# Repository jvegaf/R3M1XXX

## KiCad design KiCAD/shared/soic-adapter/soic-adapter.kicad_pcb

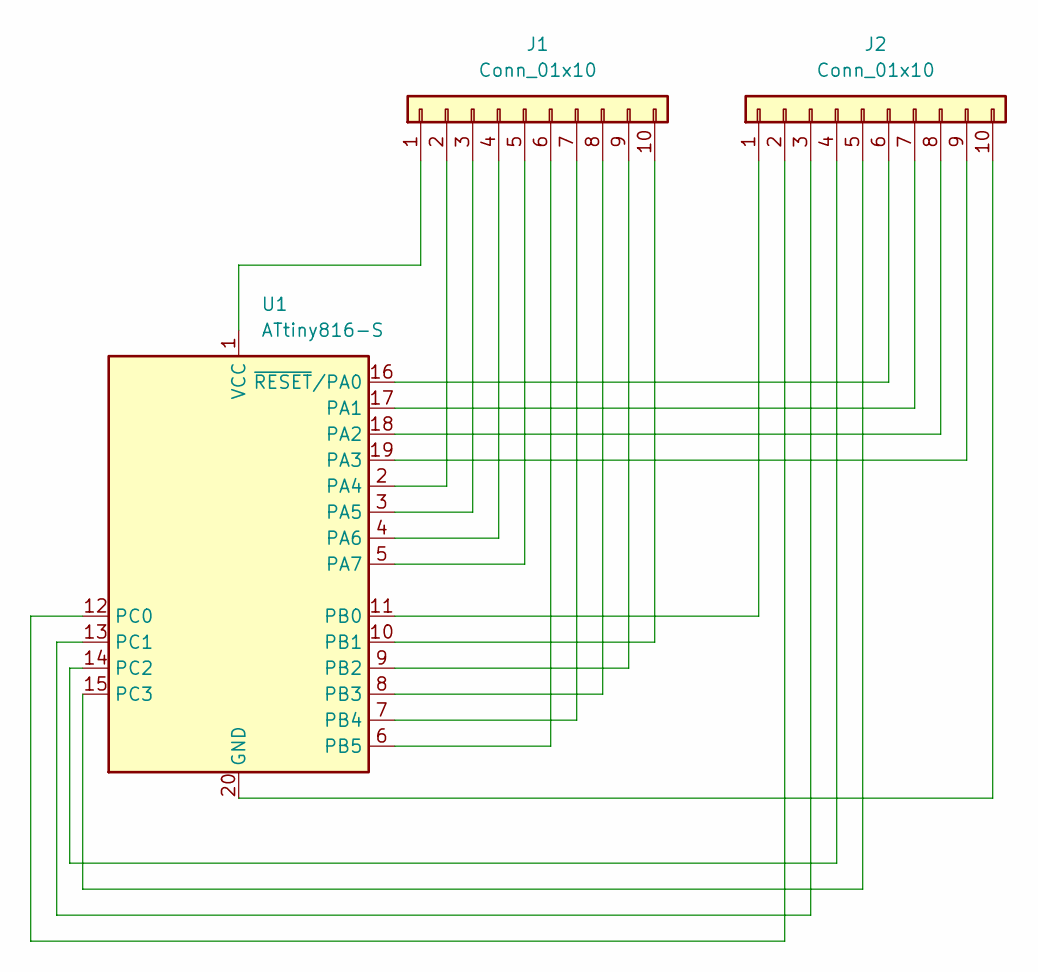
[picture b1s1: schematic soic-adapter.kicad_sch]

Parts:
J1: Conn_01x10; PinHeader_1x10_P2.54mm_Vertical
J2: Conn_01x10; PinSocket_1x10_P2.54mm_Vertical
U1: ATtiny816-S; SOIC-20W_7.5x12.8mm_P1.27mm

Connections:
unnamed: J1.1, U1.1 (VCC)
unnamed: J1.2, U1.2 (PA4)
unnamed: J1.3, U1.3 (PA5)
unnamed: J1.4, U1.4 (PA6)
unnamed: J1.5, U1.5 (PA7)
unnamed: J1.6, U1.6 (PB5)
unnamed: J1.7, U1.7 (PB4)
unnamed: J1.8, U1.8 (PB3)
unnamed: J1.9, U1.9 (PB2)
unnamed: J1.10, U1.10 (PB1)
unnamed: J2.1, U1.11 (PB0)
unnamed: J2.2, U1.12 (PC0)
unnamed: J2.3, U1.13 (PC1)
unnamed: J2.4, U1.14 (PC2)
unnamed: J2.5, U1.15 (PC3)
unnamed: J2.6, U1.16 (~RESET/PA0)
unnamed: J2.7, U1.17 (PA1)
unnamed: J2.8, U1.18 (PA2)
unnamed: J2.9, U1.19 (PA3)
unnamed: J2.10, U1.20 (GND)

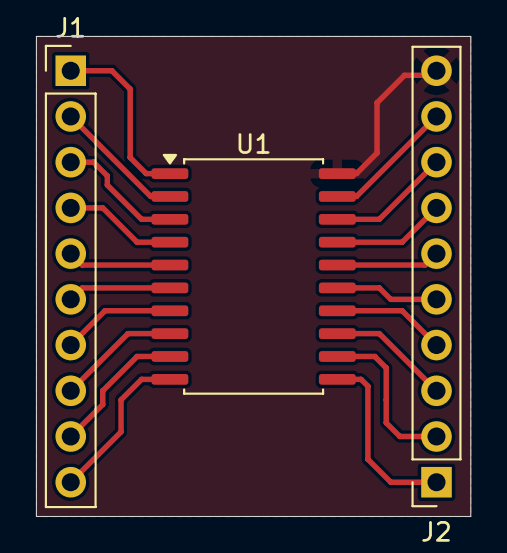
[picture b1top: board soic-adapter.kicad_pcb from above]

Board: 2 copper layers, 24.1 x 26.7 mm, 3 parts (0 on the bottom side), 20 nets.

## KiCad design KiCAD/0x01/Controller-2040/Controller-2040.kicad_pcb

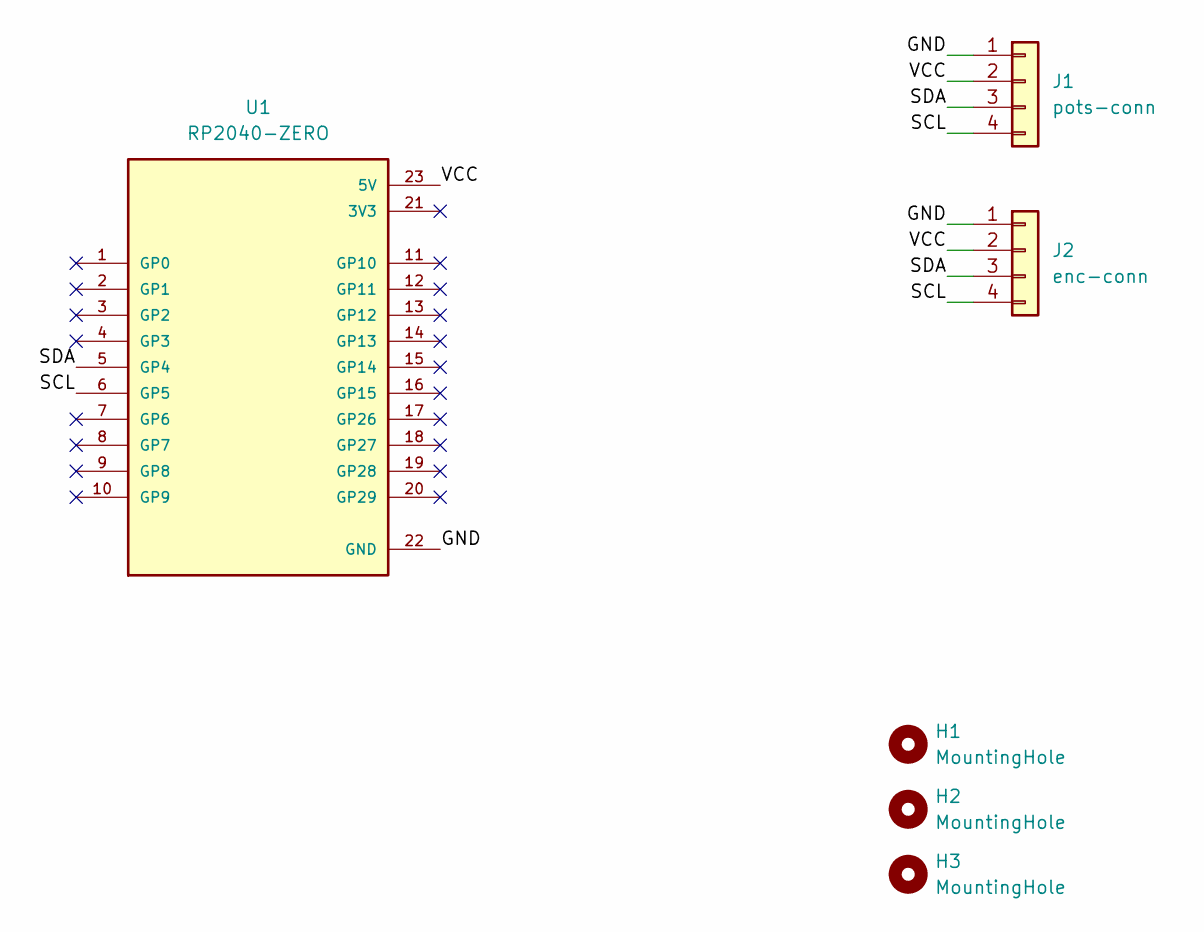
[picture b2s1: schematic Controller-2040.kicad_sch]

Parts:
H1, H2, H3: MountingHole; MountingHole_3.2mm_M3
J1: pots-conn; JST_PH_S4B-PH-K_1x04_P2.00mm_Horizontal
J2: enc-conn; JST_PH_S4B-PH-K_1x04_P2.00mm_Horizontal
U1: RP2040-ZERO; MODULE_RP2040-ZEROa; PARTREV NA

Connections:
/GND: J1.1, J2.1, U1.22 (GND)
/SCL: J1.4, J2.4, U1.6 (GP5)
/SDA: J1.3, J2.3, U1.5 (GP4)
/VCC: J1.2, J2.2, U1.23 (5V)

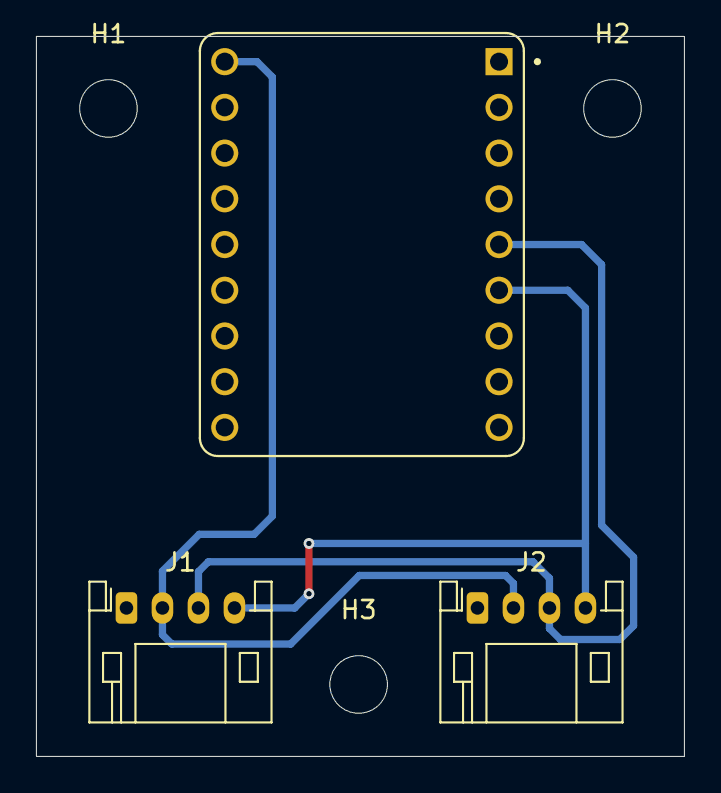
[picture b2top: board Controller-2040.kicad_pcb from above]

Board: 2 copper layers, 36.0 x 40.0 mm, 6 parts (0 on the bottom side), 4 nets.

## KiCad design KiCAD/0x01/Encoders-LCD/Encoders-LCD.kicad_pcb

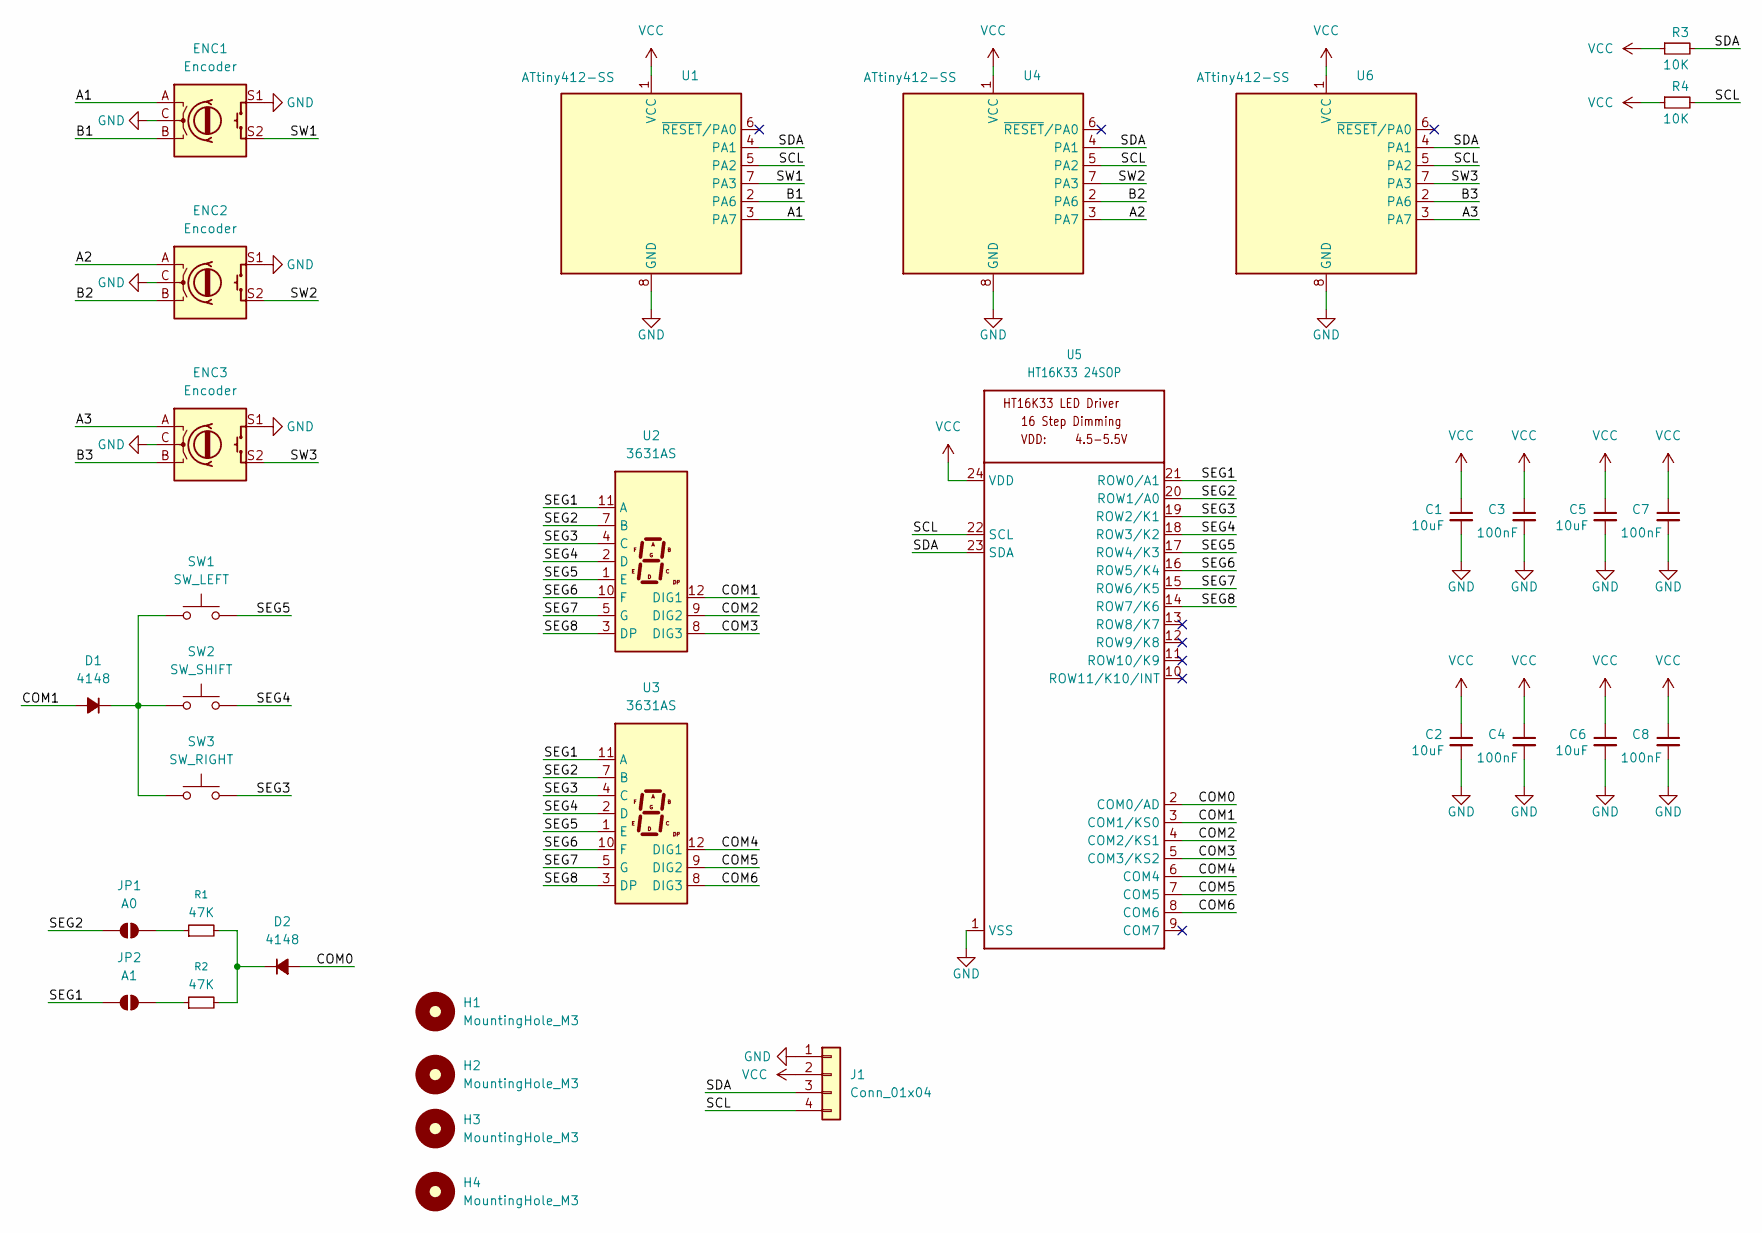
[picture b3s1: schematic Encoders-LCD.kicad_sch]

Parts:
C1, C2, C5, C6: 10uF; C_0805_2012Metric_Pad1.18x1.45mm_HandSolder
C3, C4, C7, C8: 100nF; C_0603_1608Metric_Pad1.08x0.95mm_HandSolder
D1, D2: 4148; D_SOD-123
ENC1, ENC2, ENC3: Encoder; self-RotaryEncoder_Alps_EC11E-Switch_Vertical_H20mm_Circula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
H1, H2, H3, H4: MountingHole_M3; MountingHole_3.2mm_M3
J1: Conn_01x04; JST_PH_S4B-PH-K_1x04_P2.00mm_Horizontal
JP1: A0; SolderJumper-2_P1.3mm_Open_RoundedPad1.0x1.5mm
JP2: A1; SolderJumper-2_P1.3mm_Open_RoundedPad1.0x1.5mm
R1, R2: 47K; R_0805_2012Metric_Pad1.20x1.40mm_HandSolder
R3, R4: 10K; C_0805_2012Metric_Pad1.18x1.45mm_HandSolder
SW1: SW_LEFT; SW_PUSH_6mm_H4.3mm
SW2: SW_SHIFT; SW_PUSH_6mm_H4.3mm
SW3: SW_RIGHT; SW_PUSH_6mm_H4.3mm
U1, U4, U6: ATtiny412-SS; SOIC-8_3.9x4.9mm_P1.27mm
U2, U3: 3631AS
U5: HT16K33 24SOP; SOP-24_7.5x15.4mm_P1.27mm

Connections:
/A1: ENC1.A, U1.3 (PA7)
/A2: ENC2.A, U4.3 (PA7)
/A3: ENC3.A, U6.3 (PA7)
/B1: ENC1.B, U1.2 (PA6)
/B2: ENC2.B, U4.2 (PA6)
/B3: ENC3.B, U6.2 (PA6)
/COM0: D2.2 (A), U5.2 (COM0/AD)
/COM1: D1.2 (A), U2.12 (DIG1), U5.3 (COM1/KS0)
/COM2: U2.9 (DIG2), U5.4 (COM2/KS1)
/COM3: U2.8 (DIG3), U5.5 (COM3/KS2)
/COM4: U3.12 (DIG1), U5.6 (COM4)
/COM5: U3.9 (DIG2), U5.7 (COM5)
/COM6: U3.8 (DIG3), U5.8 (COM6)
/SCL: J1.4, R4.2, U1.5 (PA2), U4.5 (PA2), U5.22 (SCL), U6.5 (PA2)
/SDA: J1.3, R3.2, U1.4 (PA1), U4.4 (PA1), U5.23 (SDA), U6.4 (PA1)
/SEG1: JP2.1 (A), U2.11 (A), U3.11 (A), U5.21 (ROW0/A1)
/SEG2: JP1.1 (A), U2.7 (B), U3.7 (B), U5.20 (ROW1/A0)
/SEG3: SW3.2, U2.4 (C), U3.4 (C), U5.19 (ROW2/K1)
/SEG4: SW2.2, U2.2 (D), U3.2 (D), U5.18 (ROW3/K2)
/SEG5: SW1.2, U2.1 (E), U3.1 (E), U5.17 (ROW4/K3)
/SEG6: U2.10 (F), U3.10 (F), U5.16 (ROW5/K4)
/SEG7: U2.5 (G), U3.5 (G), U5.15 (ROW6/K5)
/SEG8: U2.3 (DP), U3.3 (DP), U5.14 (ROW7/K6)
/SW1: ENC1.S2, U1.7 (PA3)
/SW2: ENC2.S2, U4.7 (PA3)
/SW3: ENC3.S2, U6.7 (PA3)
GND: C1.2, C2.2, C3.2, C4.2, C5.2, C6.2, C7.2, C8.2, ENC1.C, ENC1.S1, ENC2.C, ENC2.S1, ENC3.C, ENC3.S1, J1.1, U1.8 (GND), U4.8 (GND), U5.1 (VSS), U6.8 (GND)
unnamed: D1.1 (K), SW1.1, SW2.1, SW3.1
unnamed: D2.1 (K), R1.2, R2.2
unnamed: JP1.2 (B), R1.1
unnamed: JP2.2 (B), R2.1
VCC: C1.1, C2.1, C3.1, C4.1, C5.1, C6.1, C7.1, C8.1, J1.2, R3.1, R4.1, U1.1 (VCC), U4.1 (VCC), U5.24 (VDD), U6.1 (VCC)

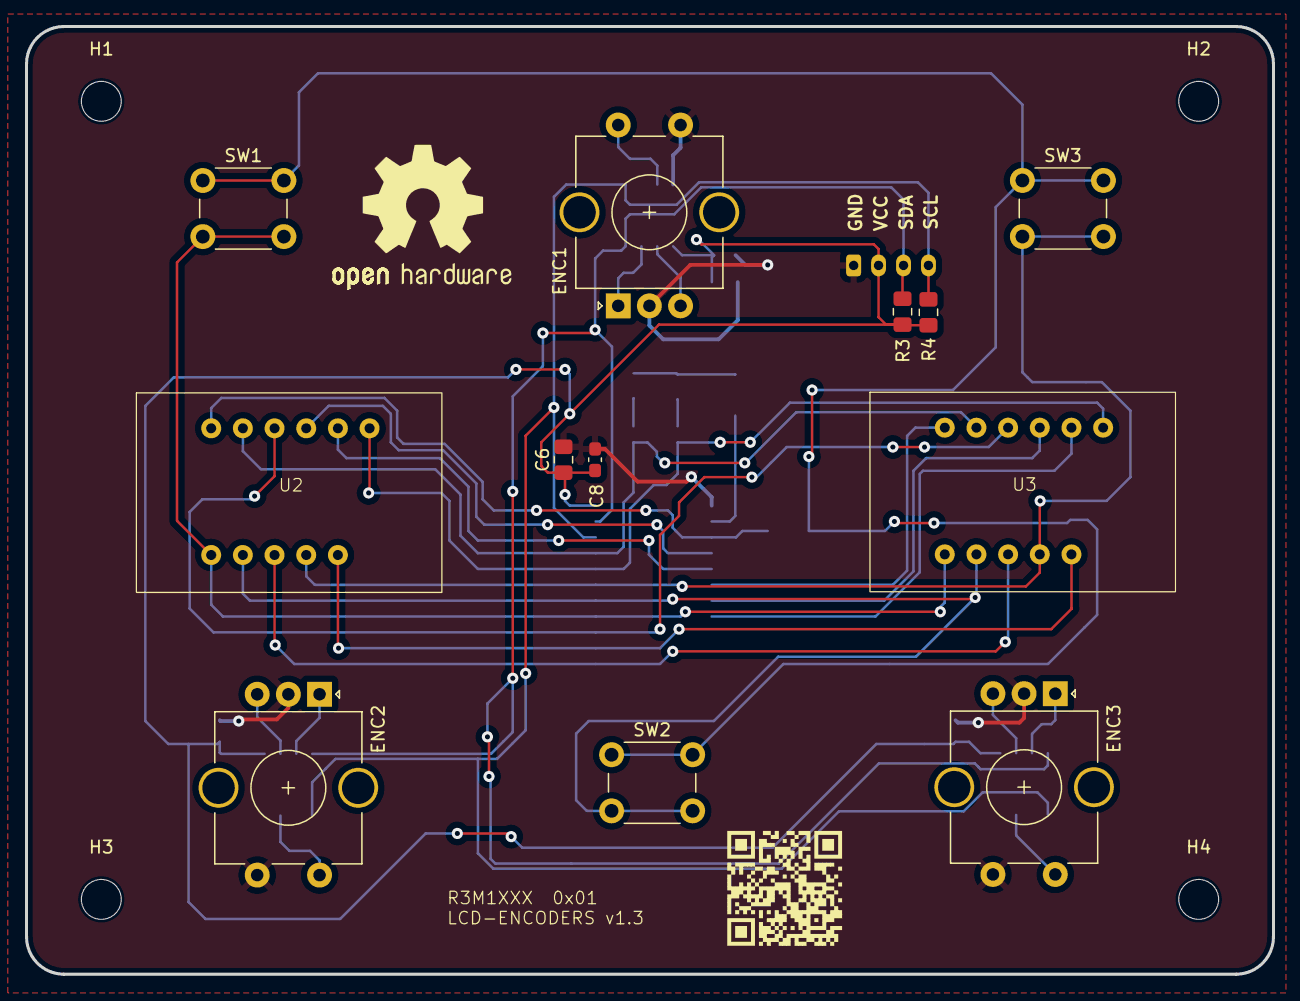
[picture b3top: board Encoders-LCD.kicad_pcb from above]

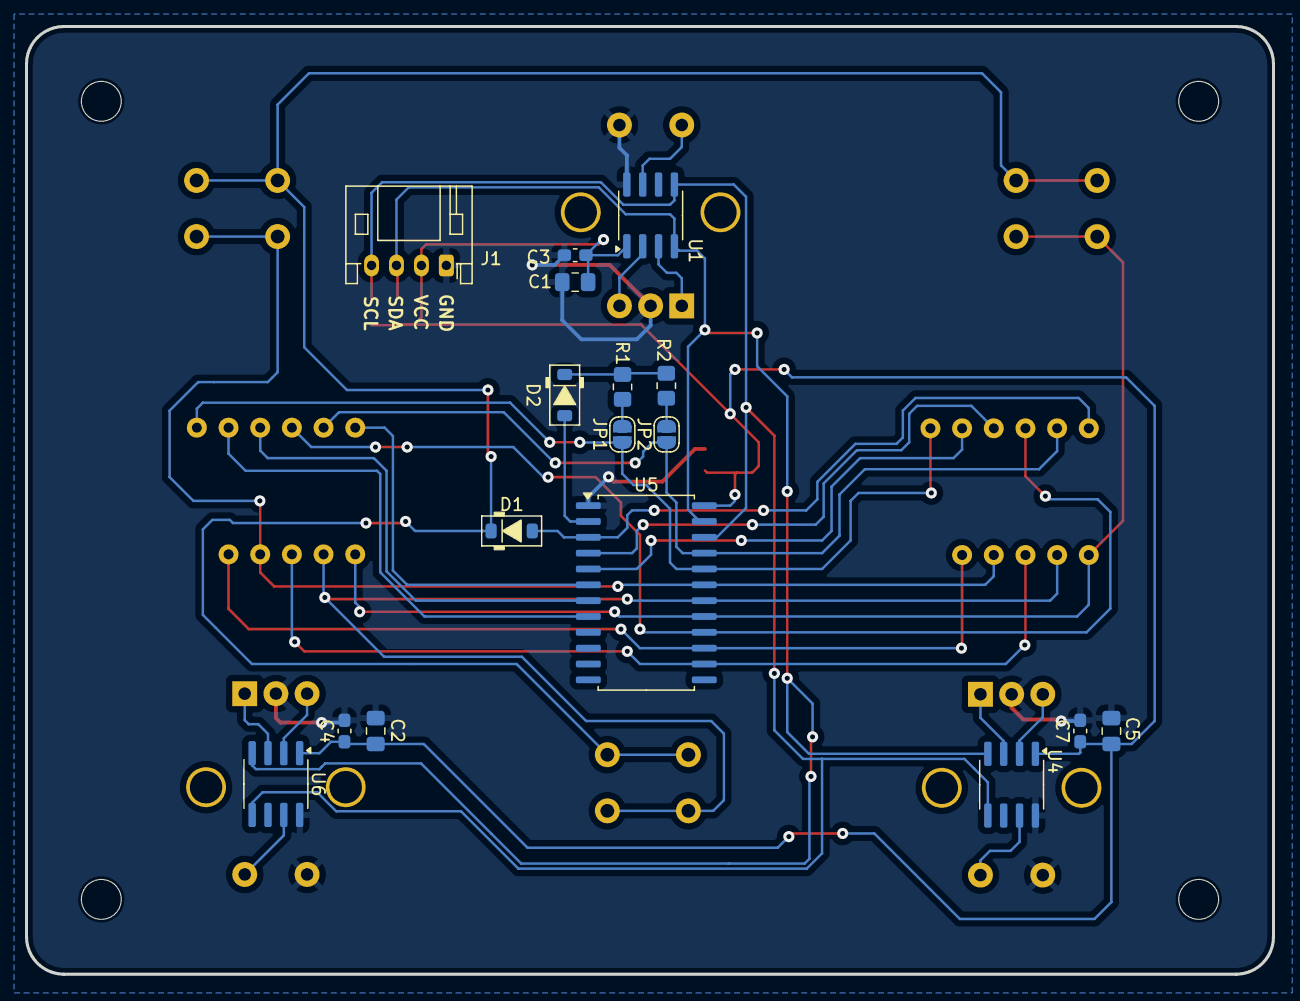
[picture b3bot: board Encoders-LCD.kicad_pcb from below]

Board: 2 copper layers, 100.0 x 76.0 mm, 33 parts (17 on the bottom side), 32 nets.

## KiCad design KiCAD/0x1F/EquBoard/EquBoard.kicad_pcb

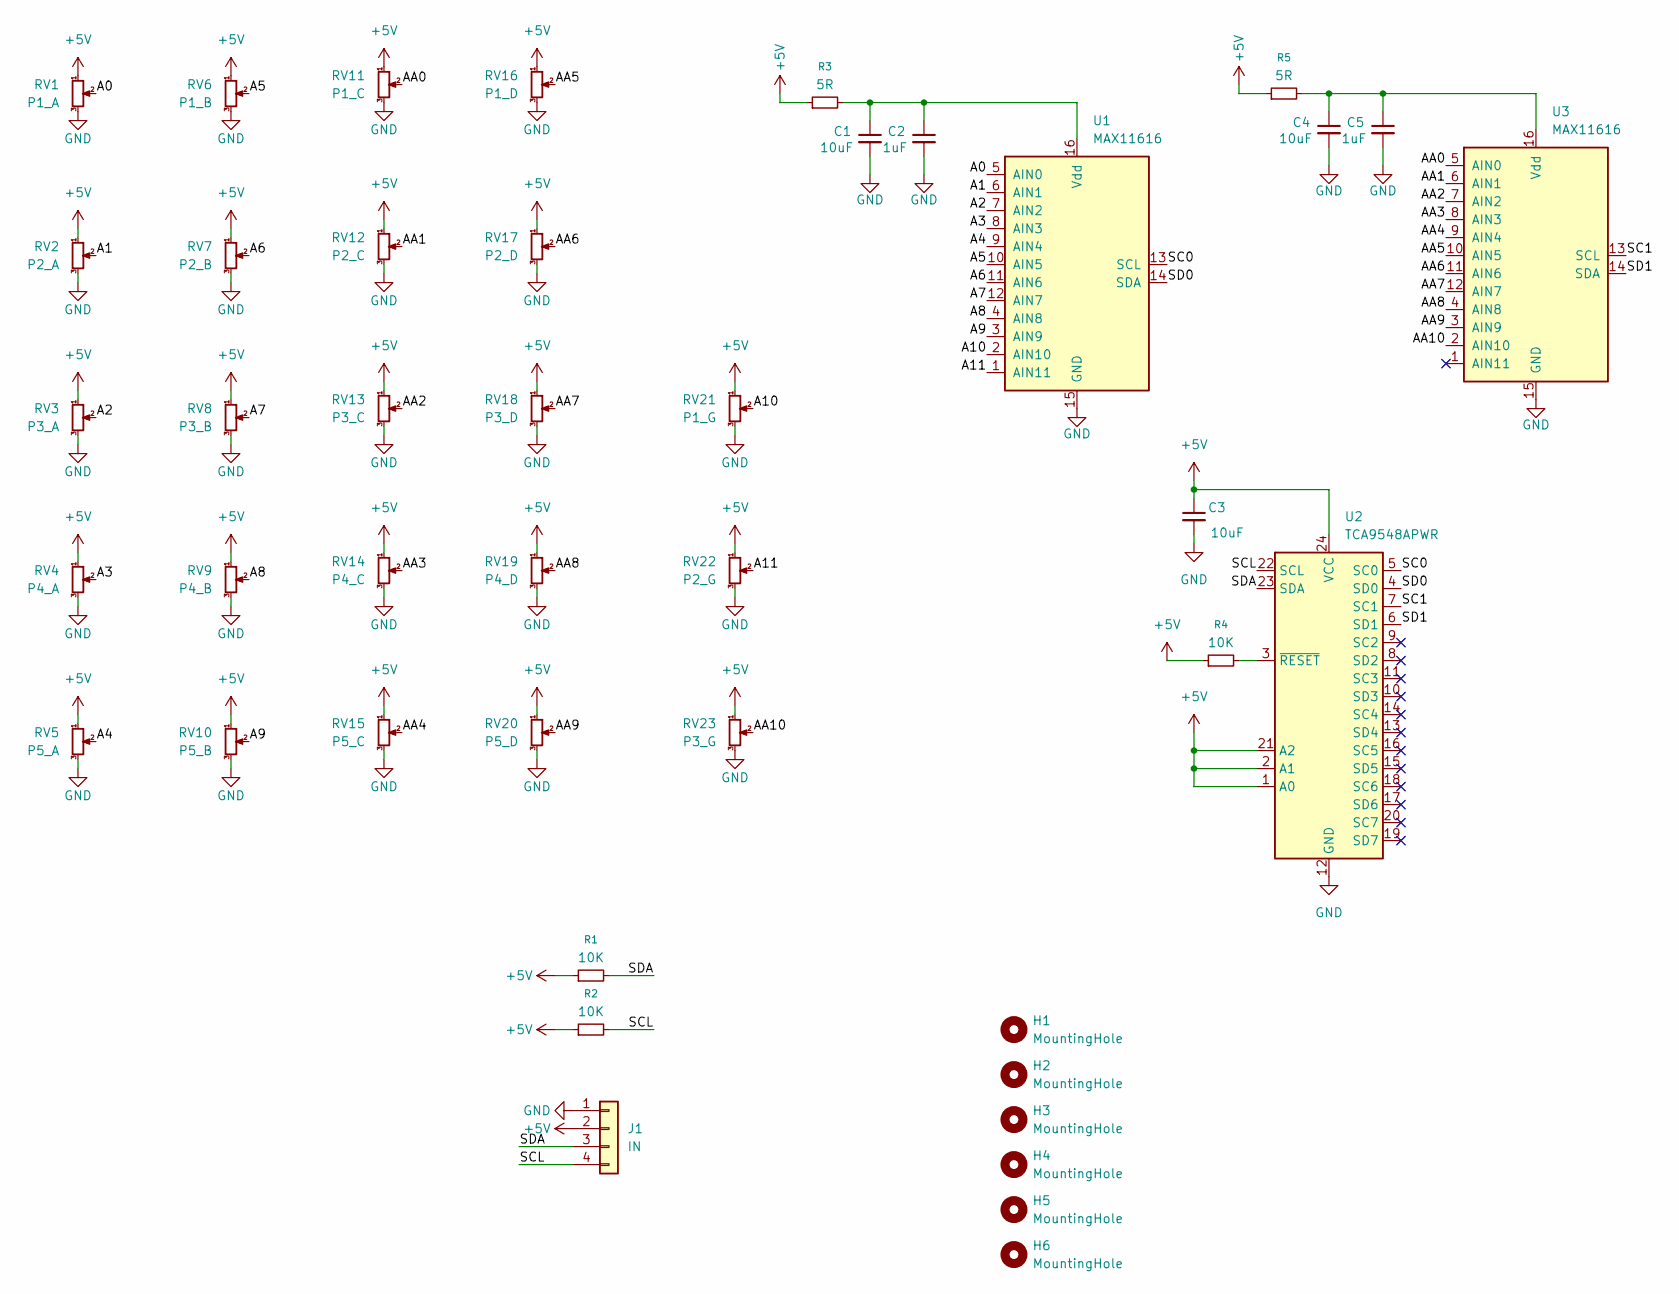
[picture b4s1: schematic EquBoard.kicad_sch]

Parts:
C1, C4: 10uF; C_0805_2012Metric_Pad1.18x1.45mm_HandSolder
C2, C5: 1uF; C_0603_1608Metric_Pad1.08x0.95mm_HandSolder
C3: 10uF; C_0603_1608Metric_Pad1.08x0.95mm_HandSolder
H1, H2, H3, H4, H5, H6: MountingHole; MountingHole_3.2mm_M3
J1: IN; JST_PH_S4B-PH-K_1x04_P2.00mm_Horizontal
R1, R2, R4: 10K; R_0805_2012Metric_Pad1.20x1.40mm_HandSolder
R3, R5: 5R; R_0805_2012Metric_Pad1.20x1.40mm_HandSolder
RV1: P1_A; Potentiometer_Bourns_PTV09A-1_Single_Vertical
RV2: P2_A; Potentiometer_Bourns_PTV09A-1_Single_Vertical
RV3: P3_A; Potentiometer_Bourns_PTV09A-1_Single_Vertical
RV4: P4_A; Potentiometer_Bourns_PTV09A-1_Single_Vertical
RV5: P5_A; Potentiometer_Bourns_PTV09A-1_Single_Vertical
RV6: P1_B; Potentiometer_Bourns_PTV09A-1_Single_Vertical
RV7: P2_B; Potentiometer_Bourns_PTV09A-1_Single_Vertical
RV8: P3_B; Potentiometer_Bourns_PTV09A-1_Single_Vertical
RV9: P4_B; Potentiometer_Bourns_PTV09A-1_Single_Vertical
RV10: P5_B; Potentiometer_Bourns_PTV09A-1_Single_Vertical
RV11: P1_C; Potentiometer_Bourns_PTV09A-1_Single_Vertical
RV12: P2_C; Potentiometer_Bourns_PTV09A-1_Single_Vertical
RV13: P3_C; Potentiometer_Bourns_PTV09A-1_Single_Vertical
RV14: P4_C; Potentiometer_Bourns_PTV09A-1_Single_Vertical
RV15: P5_C; Potentiometer_Bourns_PTV09A-1_Single_Vertical
RV16: P1_D; Potentiometer_Bourns_PTV09A-1_Single_Vertical
RV17: P2_D; Potentiometer_Bourns_PTV09A-1_Single_Vertical
RV18: P3_D; Potentiometer_Bourns_PTV09A-1_Single_Vertical
RV19: P4_D; Potentiometer_Bourns_PTV09A-1_Single_Vertical
RV20: P5_D; Potentiometer_Bourns_PTV09A-1_Single_Vertical
RV21: P1_G; Potentiometer_Bourns_PTV09A-1_Single_Vertical
RV22: P2_G; Potentiometer_Bourns_PTV09A-1_Single_Vertical
RV23: P3_G; Potentiometer_Bourns_PTV09A-1_Single_Vertical
U1, U3: MAX11616; QSOP-16_3.9x4.9mm_P0.635mm
U2: TCA9548APWR; TSSOP-24_4.4x7.8mm_P0.65mm

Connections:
+5V: C3.1, J1.2, R1.1, R2.1, R3.1, R4.1, R5.1, RV1.1, RV2.1, RV3.1, RV4.1, RV5.1, RV6.1, RV7.1, RV8.1, RV9.1, RV10.1, RV11.1, RV12.1, RV13.1, RV14.1, RV15.1, RV16.1, RV17.1, RV18.1, RV19.1, RV20.1, RV21.1, RV22.1, RV23.1, U2.1 (A0), U2.2 (A1), U2.21 (A2), U2.24 (VCC)
/A0: RV1.2, U1.5 (AIN0)
/A1: RV2.2, U1.6 (AIN1)
/A2: RV3.2, U1.7 (AIN2)
/A3: RV4.2, U1.8 (AIN3)
/A4: RV5.2, U1.9 (AIN4)
/A5: RV6.2, U1.10 (AIN5)
/A6: RV7.2, U1.11 (AIN6)
/A7: RV8.2, U1.12 (AIN7)
/A8: RV9.2, U1.4 (AIN8)
/A9: RV10.2, U1.3 (AIN9)
/A10: RV21.2, U1.2 (AIN10)
/A11: RV22.2, U1.1 (AIN11)
/AA0: RV11.2, U3.5 (AIN0)
/AA1: RV12.2, U3.6 (AIN1)
/AA2: RV13.2, U3.7 (AIN2)
/AA3: RV14.2, U3.8 (AIN3)
/AA4: RV15.2, U3.9 (AIN4)
/AA5: RV16.2, U3.10 (AIN5)
/AA6: RV17.2, U3.11 (AIN6)
/AA7: RV18.2, U3.12 (AIN7)
/AA8: RV19.2, U3.4 (AIN8)
/AA9: RV20.2, U3.3 (AIN9)
/AA10: RV23.2, U3.2 (AIN10)
/SC0: U1.13 (SCL), U2.5 (SC0)
/SC1: U2.7 (SC1), U3.13 (SCL)
/SCL: J1.4, R2.2, U2.22 (SCL)
/SD0: U1.14 (SDA), U2.4 (SD0)
/SD1: U2.6 (SD1), U3.14 (SDA)
/SDA: J1.3, R1.2, U2.23 (SDA)
GND: C1.2, C2.2, C3.2, C4.2, C5.2, J1.1, RV1.3, RV2.3, RV3.3, RV4.3, RV5.3, RV6.3, RV7.3, RV8.3, RV9.3, RV10.3, RV11.3, RV12.3, RV13.3, RV14.3, RV15.3, RV16.3, RV17.3, RV18.3, RV19.3, RV20.3, RV21.3, RV22.3, RV23.3, U1.15 (GND), U2.12 (GND), U3.15 (GND)
unnamed: C1.1, C2.1, R3.2, U1.16 (Vdd)
unnamed: R4.2, U2.3 (~RESET)
unnamed: C4.1, C5.1, R5.2, U3.16 (Vdd)

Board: 2 copper layers, 43 parts (5 on the bottom side), 34 nets, no tracks yet.

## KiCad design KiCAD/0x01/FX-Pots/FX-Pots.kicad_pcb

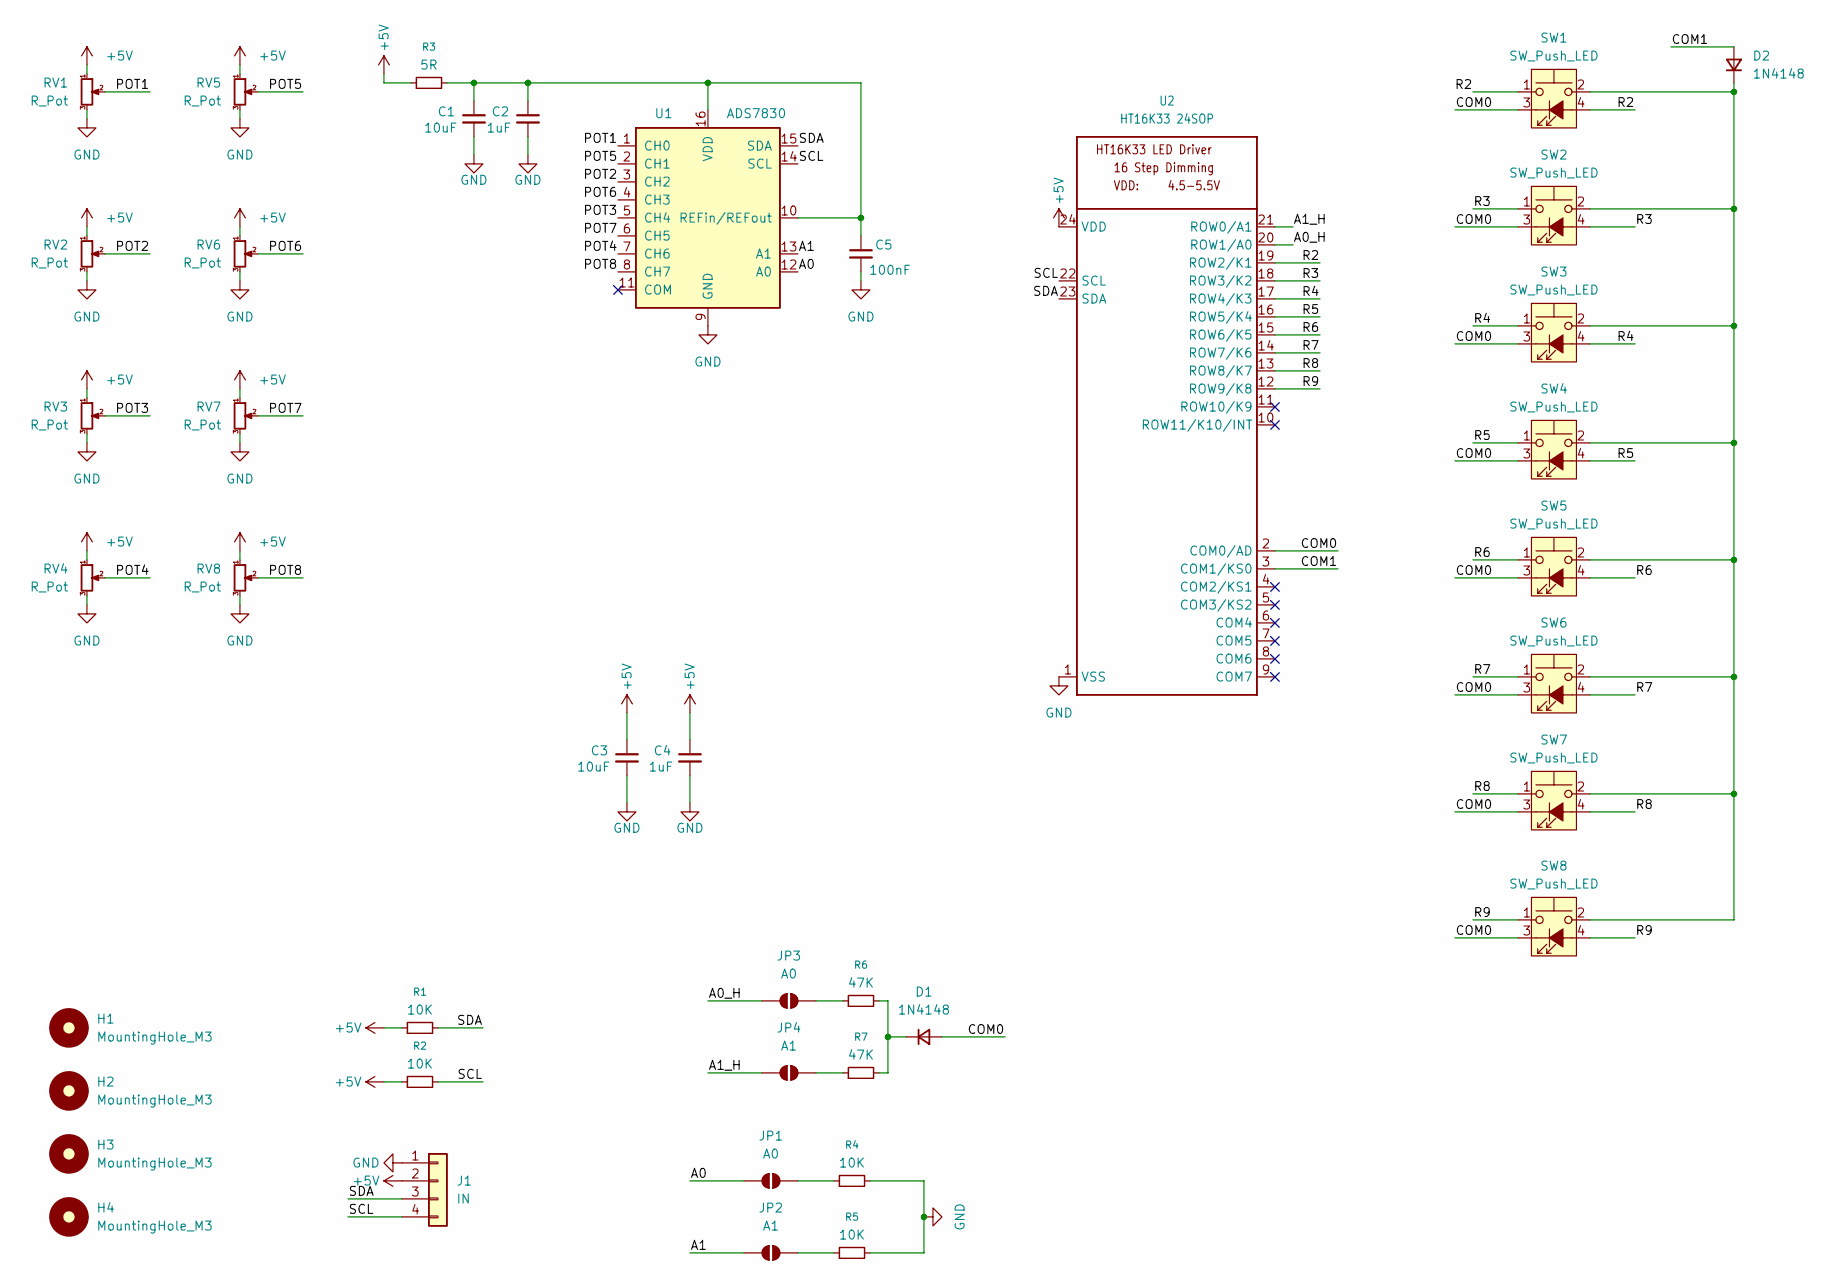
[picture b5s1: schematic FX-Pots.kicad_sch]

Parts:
C1, C3: 10uF; C_0805_2012Metric_Pad1.18x1.45mm_HandSolder
C2, C4: 1uF; C_0603_1608Metric_Pad1.08x0.95mm_HandSolder
C5: 100nF; C_0603_1608Metric_Pad1.08x0.95mm_HandSolder
D1, D2: 1N4148; D_SOD-123F
H1, H2, H3, H4: MountingHole_M3; MountingHole_3.2mm_M3
J1: IN; JST_PH_S4B-PH-K_1x04_P2.00mm_Horizontal
JP1, JP3: A0; SolderJumper-2_P1.3mm_Open_RoundedPad1.0x1.5mm
JP2, JP4: A1; SolderJumper-2_P1.3mm_Open_RoundedPad1.0x1.5mm
R1, R2, R4, R5: 10K; R_0805_2012Metric_Pad1.20x1.40mm_HandSolder
R3: 5R; R_0805_2012Metric_Pad1.20x1.40mm_HandSolder
R6, R7: 47K; R_0805_2012Metric_Pad1.20x1.40mm_HandSolder
RV1, RV2, RV3, RV4, RV5, RV6, RV7, RV8: R_Pot; Potentiometer_Bourns_PTV09A-1_Single_Vertical
SW1, SW2, SW3, SW4, SW5, SW6, SW7, SW8: SW_Push_LED; SW_PUSH_6mm_LED
U1: ADS7830; TSSOP-16_4.4x5mm_P0.65mm
U2: HT16K33 24SOP; SOIC-24W_7.5x15.4mm_P1.27mm

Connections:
+5V: C3.1, C4.1, J1.2, R1.1, R2.1, R3.1, RV1.1, RV2.1, RV3.1, RV4.1, RV5.1, RV6.1, RV7.1, RV8.1, U2.24 (VDD)
/A0: JP1.1 (A), U1.12 (A0)
/A0_H: JP3.1 (A), U2.20 (ROW1/A0)
/A1: JP2.1 (A), U1.13 (A1)
/A1_H: JP4.1 (A), U2.21 (ROW0/A1)
/COM0: D1.2 (A), SW1.3 (K), SW2.3 (K), SW3.3 (K), SW4.3 (K), SW5.3 (K), SW6.3 (K), SW7.3 (K), SW8.3 (K), U2.2 (COM0/AD)
/COM1: D2.2 (A), U2.3 (COM1/KS0)
/POT1: RV1.2, U1.1 (CH0)
/POT2: RV2.2, U1.3 (CH2)
/POT3: RV3.2, U1.5 (CH4)
/POT4: RV4.2, U1.7 (CH6)
/POT5: RV5.2, U1.2 (CH1)
/POT6: RV6.2, U1.4 (CH3)
/POT7: RV7.2, U1.6 (CH5)
/POT8: RV8.2, U1.8 (CH7)
/R2: SW1.1, SW1.4 (A), U2.19 (ROW2/K1)
/R3: SW2.1, SW2.4 (A), U2.18 (ROW3/K2)
/R4: SW3.1, SW3.4 (A), U2.17 (ROW4/K3)
/R5: SW4.1, SW4.4 (A), U2.16 (ROW5/K4)
/R6: SW5.1, SW5.4 (A), U2.15 (ROW6/K5)
/R7: SW6.1, SW6.4 (A), U2.14 (ROW7/K6)
/R8: SW7.1, SW7.4 (A), U2.13 (ROW8/K7)
/R9: SW8.1, SW8.4 (A), U2.12 (ROW9/K8)
/SCL: J1.4, R2.2, U1.14 (SCL), U2.22 (SCL)
/SDA: J1.3, R1.2, U1.15 (SDA), U2.23 (SDA)
GND: C1.2, C2.2, C3.2, C4.2, C5.2, J1.1, R4.2, R5.2, RV1.3, RV2.3, RV3.3, RV4.3, RV5.3, RV6.3, RV7.3, RV8.3, U1.9 (GND), U2.1 (VSS)
unnamed: D1.1 (K), R6.2, R7.2
unnamed: D2.1 (K), SW1.2, SW2.2, SW3.2, SW4.2, SW5.2, SW6.2, SW7.2, SW8.2
unnamed: JP1.2 (B), R4.1
unnamed: JP2.2 (B), R5.1
unnamed: JP3.2 (B), R6.1
unnamed: JP4.2 (B), R7.1
unnamed: C1.1, C2.1, C5.1, R3.2, U1.10 (REFin/REFout), U1.16 (VDD)

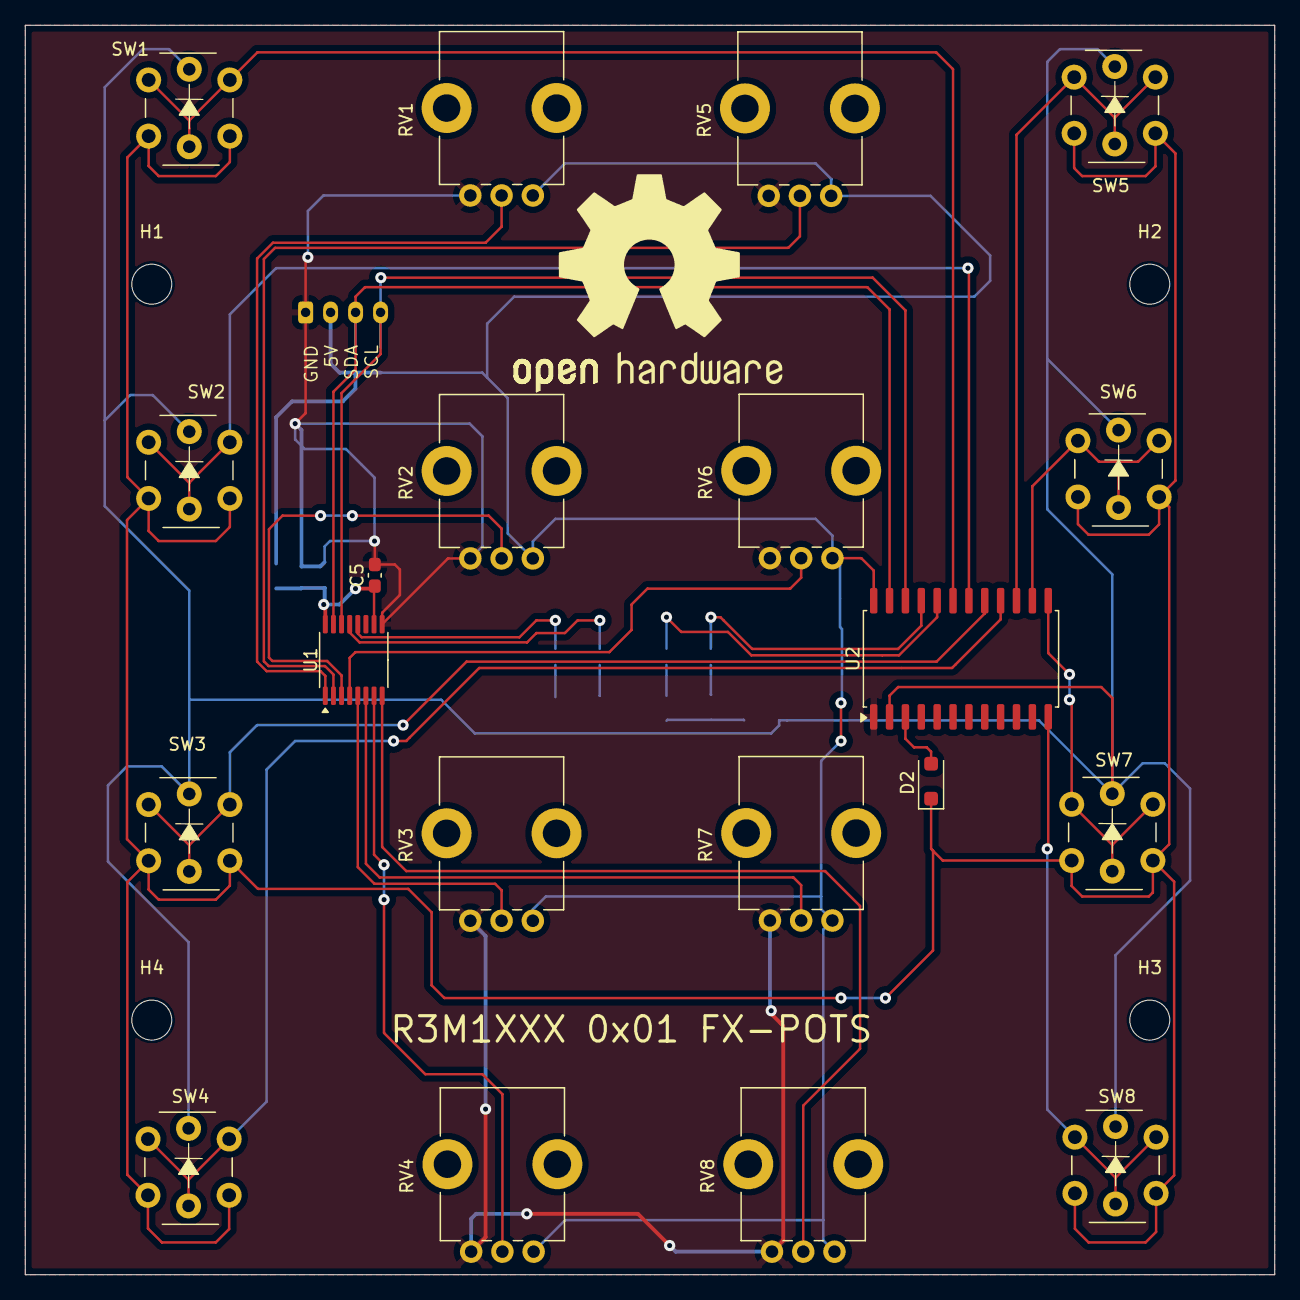
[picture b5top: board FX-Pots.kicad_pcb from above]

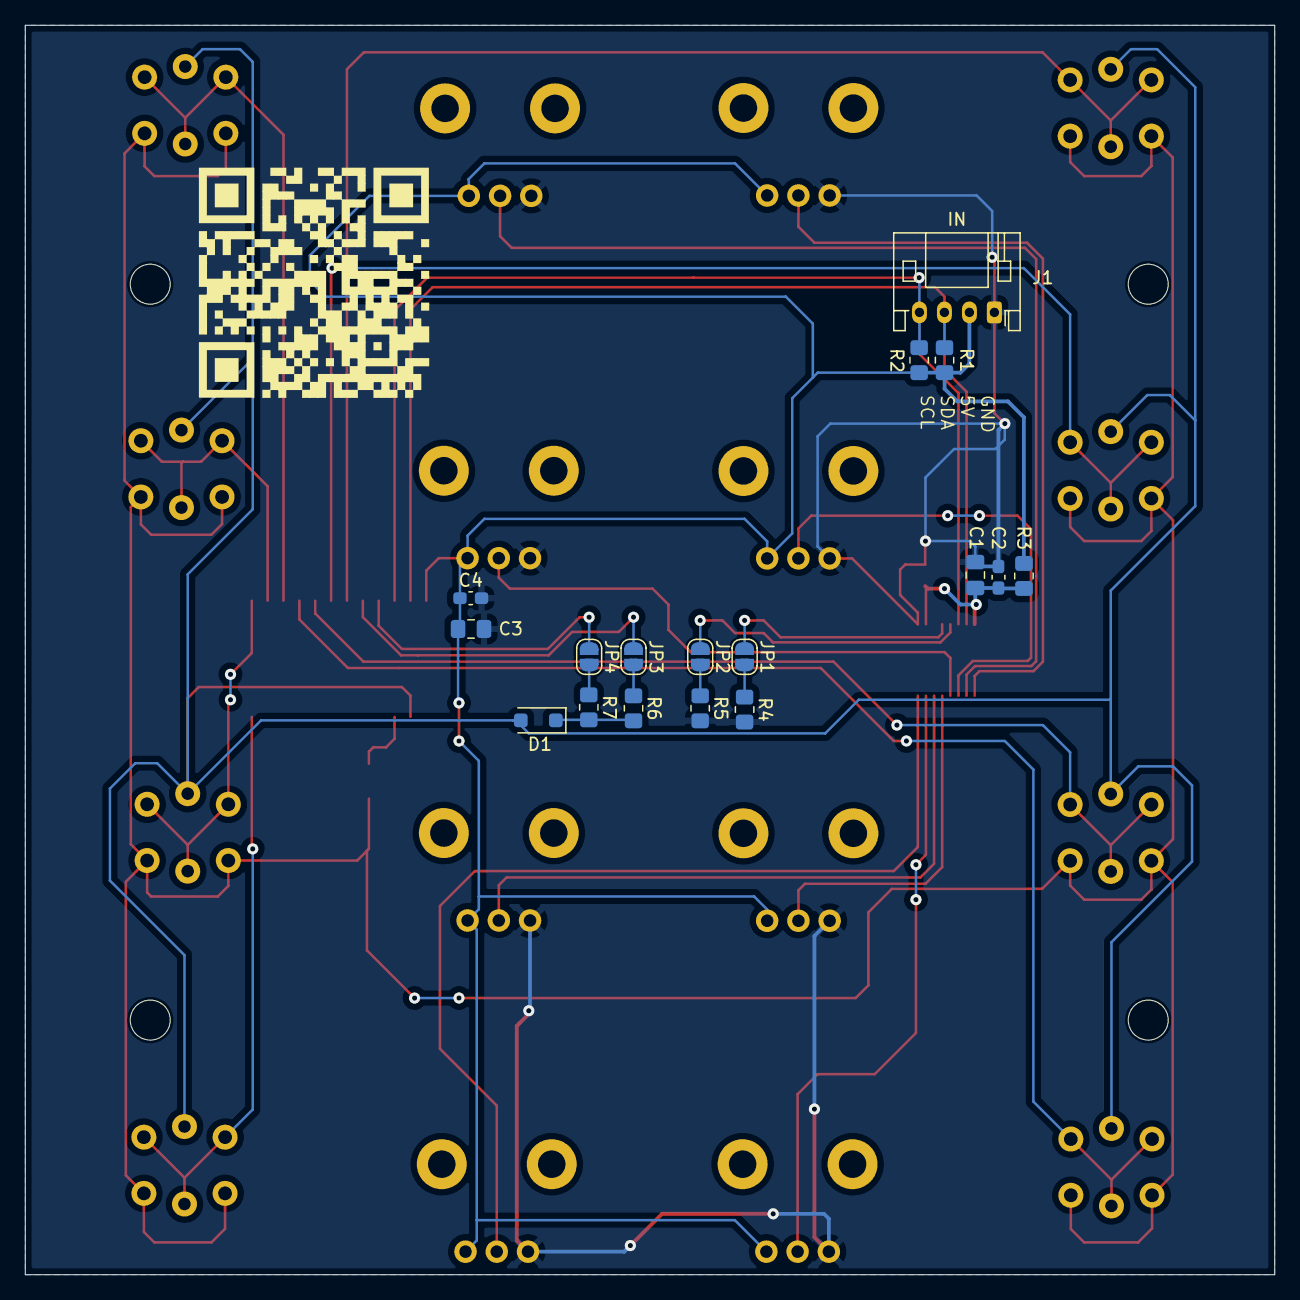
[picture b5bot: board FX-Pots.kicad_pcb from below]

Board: 2 copper layers, 100.0 x 100.0 mm, 41 parts (17 on the bottom side), 33 nets.
